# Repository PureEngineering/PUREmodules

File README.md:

# PUREmodules

This is example code to help you get started with PUREmodules

check out www.pureengineering.com and www.puremodules.com for more information

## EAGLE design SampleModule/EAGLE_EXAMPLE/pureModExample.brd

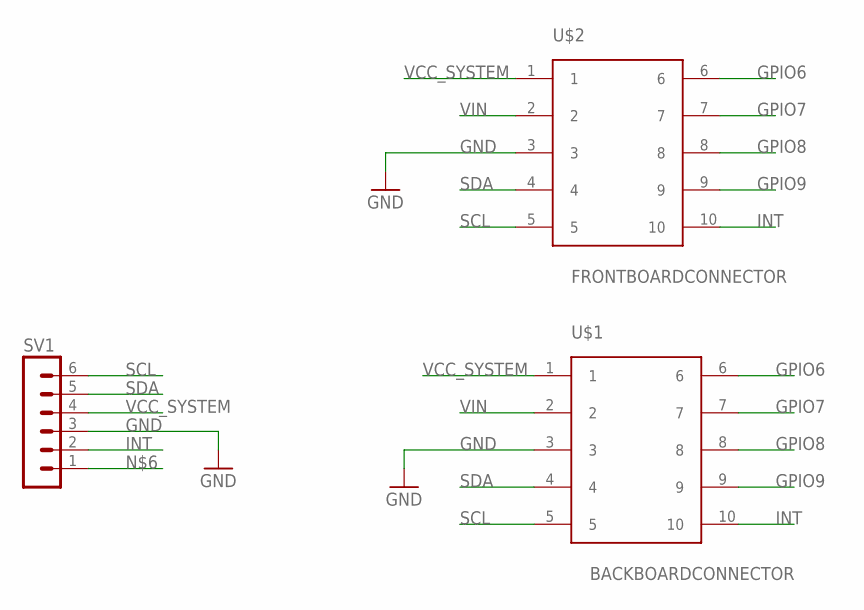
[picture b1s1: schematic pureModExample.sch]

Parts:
SV1: MA06-1
U$1: BACKBOARDCONNECTOR
U$2: FRONTBOARDCONNECTOR

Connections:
GND: SV1.3, U$1.3, U$2.3
GPIO6: U$1.6, U$2.6
GPIO7: U$1.7, U$2.7
GPIO8: U$1.8, U$2.8
GPIO9: U$1.9, U$2.9
INT: SV1.2, U$1.10, U$2.10
SCL: SV1.6, U$1.5, U$2.5
SDA: SV1.5, U$1.4, U$2.4
VCC_SYSTEM: SV1.4, U$1.1, U$2.1
VIN: U$1.2, U$2.2

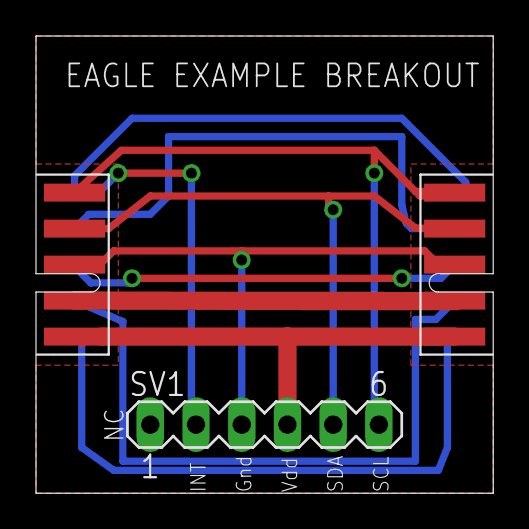
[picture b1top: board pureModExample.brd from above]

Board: 2 copper layers, 25.4 x 25.4 mm, 3 parts (0 on the bottom side), 10 nets.

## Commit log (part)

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2016-09-11 added sample modules
2016-10-13 Added two Arduino code example to readout the basic registers to make sure the chips are working correctly.
2016-10-13 code format
2016-10-13 fixed name
2016-10-14 added more code. still not working fully.
2017-01-14 added code from https://github.com/schizobovine/APDS9250, but with IC check logic flipped
2017-01-14 added simple example for LIS2DE12 to read out accelerometer data
2017-01-14 added readme
2017-01-23 Adding Lis3mdl final Demo Code
2017-01-24 Si1153 final Demo Code
2017-01-30 Si1153 Arduino Library
2017-01-30 Format Si1153.cpp
2017-01-31 Added Arduino Accelerometer Code
2017-01-31 Fixed Structure of Time Of Flight Sensor. Not fully working yet.
2017-01-31 This code tests the SuperSensor's ProxSensor, Magnetometer and Accelerometer using Serial Port. Also displays reference registers for ToF sensor.
2017-01-31 Deleted the wrong formatted files
2017-02-01 Fixed the Channel 3 bug and Matched the function names to the other ones.
2017-02-01 Added Fully Working Arduino Code for BME280
2017-02-01 Fixed Bug in Initialize function
2017-02-01 Small bug
2017-02-01 Abstracted the initialization settings. Fully Working
2017-02-02 added bat file.
2017-02-05 Small changes to Accelerometer.
2017-02-08 Structure change on all sensors. Got BME280 working on nrf52
2017-02-10 Added abstraction layer to Magnetometer nrf code.
2017-02-10 Small bug in Accelerometer code
2017-02-11 Magnetometer ready for code review.
2017-02-11 UVA code ready for code review
2017-02-11 Updated Main to run new code.
2017-02-11 Magnetometer Code ready for code review
2017-02-11 Accelerometer Arduino code ready for Code Review
2017-02-11 Fixed typo bug in UV sensor.
2017-02-13 Added Makefile that pulls SDK. Changed Directory structure to match it.
2017-02-13 readme
2017-02-16 Changes to the MakeFile
2017-02-18 added private.pem file
2017-02-18 added simple prox demo for puremodules.
2017-02-18 updated so you flash the softdevice as well.
2017-02-18 added some examples.
2017-02-18 added custom board config for the nrf52 puremoudles core module
2017-03-03 Code Displays Pass/Fail prompts for sensors.
2017-03-10 CoreModule code adapted to SuperSensor Structure. Running basic code that reads accelerometer data every second.
2017-03-10 Changed the Structure of the Code to share one Modules_library. OnboardCode works with the library.
2017-03-11 removed while loops from the code, so it wouldn't get locked up on a missing or bad chip.
2017-03-12 added basic si1153 demo
2017-03-12 changed case
2017-03-12 moved folders to right location.
2017-03-12 made folders lowercase
2017-03-12 added proximity example
2017-03-12 changed project name
2017-03-12 file reformat, and fixed build
2017-03-12 added some code from the datasheet, to turn on the green led.
2017-03-13 Fixed the library dependencies.
2017-03-13 Removed all compiler warnings from library.
2017-03-13 Basic Algo for counting steps.
2017-03-28 Added BLE Supersensor -> android interface.
2017-03-31 Android app
2017-03-31 Added some power down functions and fixed some warnings.
2017-04-05 Timers for sending data added.
2017-04-06 Skeleton of assertion test code.
2017-04-06 Code used to interface with android application
2017-04-06 Cleaned up BLE handler. Removed some older projects not used anymore.
2017-04-07 Small style changes. Added Supersensor powerdown function that sleeps all sensors.
2017-04-08 fixed Case of function calls.
2017-04-11 added very basic apds9250 test code to verify sensor is soldered properly.
2017-04-11 added apds9250 to makefile.
2017-04-12 More verbose pass/fail outputs. Started addition of apds9250 and vl53l0 interface with android app.
2017-04-12 Updated UART app to include APDS9250 and Vl53l0
2017-04-15 added auto switching to core module sensor if external one is not detected. this way the code can be used on both with and without the supersensor
2017-04-16 added bat file, that shows how to merge and flash the bootloader in one step.
2017-04-16 added built hex file of the bootloader so it can be referenced elsewhere when merging the application with the bootloader.
2017-04-16 switch to using timer instead of delay loop to save power. Added slow interval so you can still connect after a long period.
2017-04-21 added merged app, used for testing and shipping with the nrf52 core modules.
2017-04-22 added start of driver (untested)
2017-04-24 modification of the test app to get rid of the printf. added 's' state to the supersensor test. modified the led blink to have 10 blinks on pass.
2017-04-25 Completed apds9250 library
2017-04-26 Added run_apds9250 and run_apds9250_ble. APDS9250 Code should be done.
2017-04-26 Fixed Compiler warnings (untested)
2017-04-26 Added sleep function (untested)
2017-04-26 apds9250, p1234701ct BLE library complete (untested)
2017-04-26 Added apds9250 and p1234701ct to uart app
2017-04-26 Added p1234701ct to supersensor.c code
2017-04-27 Android app added
2017-05-04 added ability to change integration time.
2017-05-09 Keys for DFU
2017-05-09 Fixed bug in Setup code.
2017-05-09 Correctly prints RGB values now.
2017-05-10 Removed pt1234701ct from supersensor code.
2017-05-14 Removed extra private.pem that isnt being used.
2017-05-15 Changed public key to match the key on shipped CoreModules
2017-05-15 Changed program code from absolute to relative path.
2017-05-15 Fixed path
2017-06-01 added hardware schematics
2017-06-27 Fixed printout of BME280 altitude
2017-06-30 Starting project to test pureHealth functionality
2017-07-05 Added arduino library for TMP007
2017-07-05 Arduino tmp007 library
2017-07-05 Completed tmp007 driver (untested)
2017-07-05 Project to quickly test tmp007 driver (untested)
2017-07-06 Drivers for 16 bit ADC Ads1114 (Untested)
2017-07-19 SI1153_BLE_TEST1
2017-07-19 created a new folder called si1153_ble_test, which receive data using BLE
2017-07-20 si1153 can receive data from phone using BLE
2017-07-20 Source code for Android app
2017-07-20 Start of capacitive sensor code
2017-07-21 %5d, %5d, %5d\n is the packet, length is 20
2017-07-25 Finalized fdc2214 (untested)
2017-07-25 Project to test fdc2214
2017-07-25 Getting all the sensor data on the si1153 and plot it on the phone, currently able to plot the si1153 channel 1 and lis2de x-axis, sending 36 characters to the phone %5d,%5d,%5d,%5d,%5d,%5d\n, first 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
2017-07-26 graphing si1153 and lis2de using the android app, packets: %5d,%5d,%5d,%05d,%05d,%05d\n
2017-07-26 removed the android BLEDataLogger from nrf52 folder
2017-07-28 grid eye nrf52 code
2017-07-29 added comments
2017-07-30 pureHealth android application code
2017-07-30 Added bluetooth connectivity functions to tmp007
2017-07-30 BLE functionality to fdc2214
2017-07-30 cleaned up code. changed dataformat to be hex, 0-255 range only to fit in ble frame size.
2017-07-30 added bat files to ease with flashing softdevice and code.
2017-07-30 Update README.md
    fixed link
2017-08-01 able to draw bitmap onto canvas
2017-08-02 parsed the packet, stored the temperature value into a 2d string array, changed the format of the packet in the uC side.
2017-08-02 can produce a output on the phone but can't detect objects
2017-08-03 able to broadcast data in the grideye activity, fixed the x and y axis display issue. need to fix the image moving issue
2017-08-03 ads1114 ble printout for android app
2017-08-03 sprintf format changed.
2017-08-04 fixed the UI and the log
2017-08-04 fixed precision issue in the map function, change it to blue to red color only, text is more transparent and got decimals
2017-08-04 testing if there is still merge conflict
2017-08-04 testing
2017-08-04 old grideye
2017-08-04 renamed folder
2017-08-04 si1153 apk
2017-08-04 changed app name to pure health logger
2017-08-09 Changed the i2c address for tmp007, added init functions in main, added NRF_FLOAT_MARKER. All sensor passed except FDC2214, also run_tmp00(), run_bme280() functions works fine
2017-08-09 tmp007 sometime gives output, sometime it just gives you zero. As strangeas it is, inorder for this code to output accelerometer values, you have to flash the puremodule code, turn on the acceleromet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
2017-08-10 changed %x to %d to see the values in decimal
2017-08-17 planning to create custom services, currently able to advertise
2017-08-17 added 1 characteristic, need to enable write function, stoped at step3.B nordic tutorial
2017-08-18 able to create a service, characteristic and receive data suing nrf connect app.
2017-08-18 transmit data when connects, stop transmit data when it disconnects
2017-08-18 added some comments
2017-08-18 Decoded the data on android side, able to print the correct ch1 data onto the phone
2017-08-18 changed some variable names
2017-08-22 characteristics works fine individually, but doesn't work together
2017-08-22 cleaned up firmware
2017-08-23 able to print out all 3 characteristics on the phone but loses packets
2017-08-25 can pass value from phone to nrf52
2017-08-26 working on low power, turn off led on the core module
2017-08-29 took out uart_init() turned off leds, current is around 1mA - 3mA when it is disconnected, around 9mA when it is connected
2017-08-29 removed an old file
2017-08-29 changed the android app name to Android-nRF-Puresoil_Streaming
2017-08-29 new name
2017-08-29 removed a build folder
2017-08-31 uncommented start advertise
2017-09-05 fdc polling app and apk files
2017-09-05 tracking these files
2017-09-06 delay in the button when you click it but it receives all 3 values from the nrf52
2017-09-06 deleted build file
2017-09-06 changed the color of actionbar and background
2017-09-07 added plots, able to plot ch1
2017-09-07 only send update to the phone once
2017-09-08 able to restore the app state after closing, need to set up a reset button
2017-09-08 able to save graph state after closing the app, able to reset the graph with a button
2017-09-08 able to auto zoom each time it plots a new value
2017-09-09 firmware is more reliable, fixed up the UI layout, added a background color to the graph
2017-09-12 added lsm6sdm driver
2017-09-12 added
2017-09-12 able to switch between air and mid soil graph
2017-09-12 fixed auto zoom when switching plots
2017-09-13 able to show each plotting points
2017-09-14 added 3 seek bar, need to set the progress
2017-09-14 finishing adding 3 progress bar and able to set values accordingly
2017-09-14 added a thread so no delay on the button, fixed a bug on no graph displayed at the very begining
2017-09-14 added dry warning sign feature
2017-09-15 added dry threshold and wet threshold feature
2017-09-15 able to receive every value by adding a 1000ms delay, found a new bug where the ex mark overlaps someimes
2017-09-16 generated APK files, in the application folder
2017-11-21 BME680 code and example project
2017-12-29 Code for DW1000 timestap handling.
2017-12-30 Restructure for easier time manipulation
2017-12-30 DW1000 test project. (intermediate phase)
2018-01-07 Fixed arduino getbit and setbit functions
2018-01-11 dw1000 code compiling.
2018-01-12 Spi driver to its own files
2018-01-16 uart/conns/other functionality added to template dw1000 code
2018-01-16 SPI code and all initialization functions. About to add DW1000 specific code into main
2018-01-16 Changed structure for scope of SPI variable.
2018-01-17 Full code entered into main.cpp. Two functions are causing errors
2018-01-17 Fully working code. Connected to DW1000
2018-01-18 Clean up code for use in testing the core module alone
2018-01-18 removed unused code from core_accel tester
2018-01-18 nrf52 dw1000 code
2018-01-18 Creating TX code (not fully working)
2018-01-18 Cleared all warnings
2018-01-19 TX has a string error
2018-01-19 dw1000 tx compiling
2018-01-19 dw1000 transmit code
2018-01-19 DW1000 RX code complete, no warnings.
2018-01-22 Added ble code back to prepare for android app
2018-01-22 added ble to rx code
2018-01-29 Code for testing all the CoreModules
2018-01-31 started the UI for the toybot
2018-01-31 removed toybot
2018-02-06 Setup dw1000 as tag almost complete
2018-04-10 Just accidently deleted the entire dwm project. Other changes are here though
2018-04-10 Removed projects that were nonworking attempts
2018-04-12 uart
2018-04-13 Removed uart
